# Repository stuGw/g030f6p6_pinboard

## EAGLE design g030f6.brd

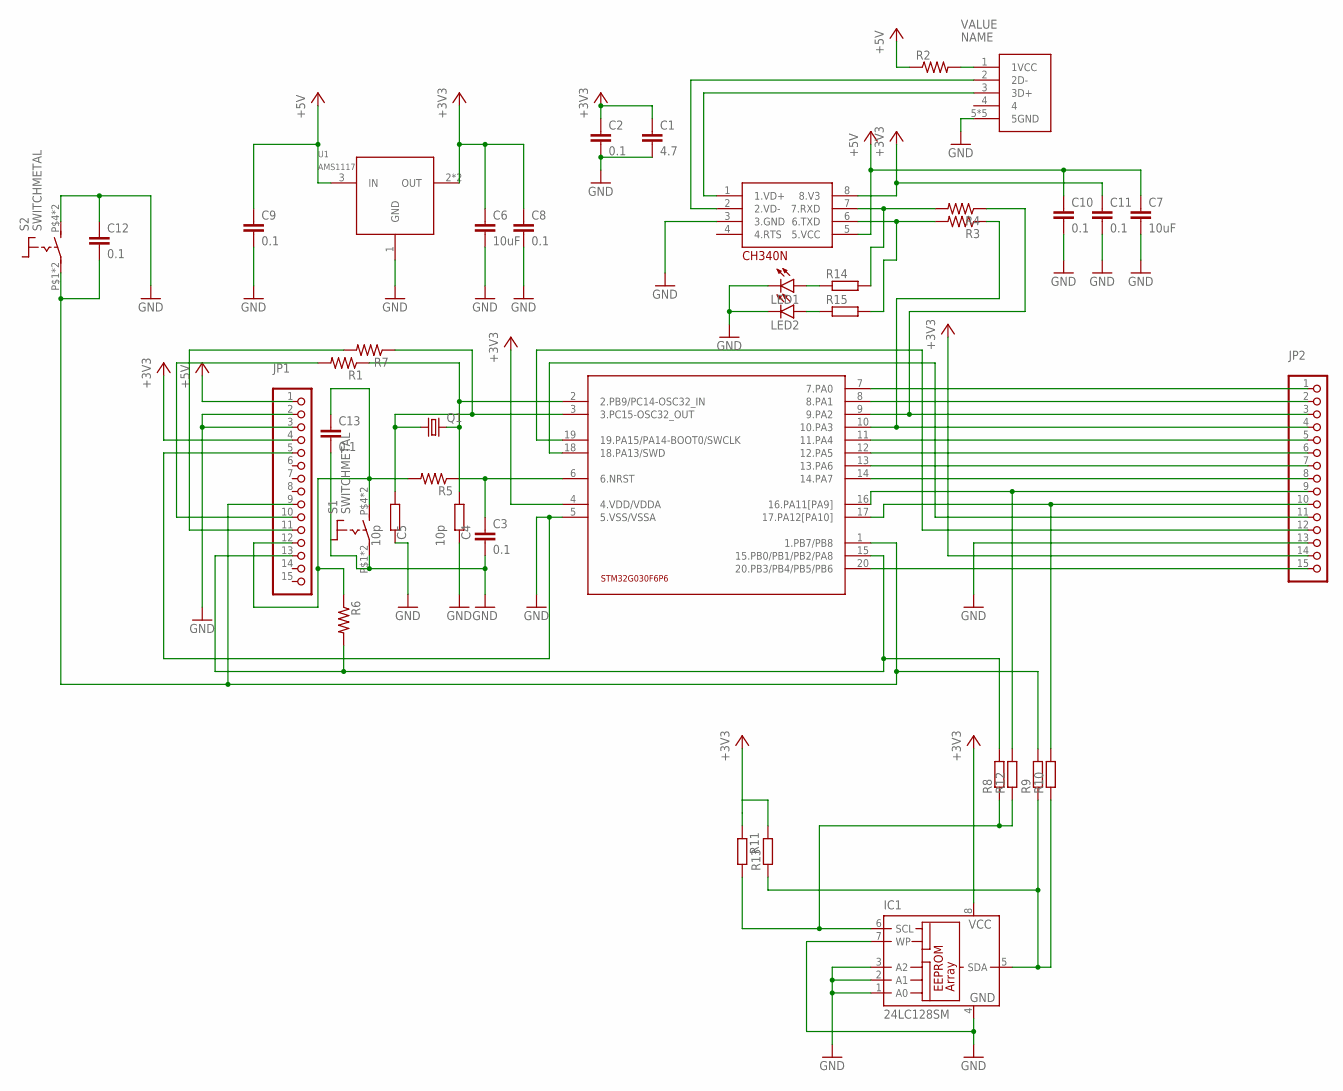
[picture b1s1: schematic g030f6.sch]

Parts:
C1: 4.7; C0805
C2, C3, C8, C9, C10, C11, C12, C13: 0.1; C0402
C4, C5: 10p; R0402
C6, C7: 10uF; C0805
CONN1: MICROUSB; MICROUSB5
IC1: 24LC128SM; SO-08M
JP1, JP2: PINHD-1X15; 1X15
LED1, LED2: LEDSML0603; SML0603
Q1: CRYSTALTC26V; TC26V
R1, R3, R4, R5, R6, R7: R-US_R0402; R0402
R2: R-US_R2010; R2010
R8, R9, R10, R11, R12, R13: R-EU_R0603; R0603
R14, R15: R-EU_R0402; R0402
S1, S2: SWITCHMETAL; SWMET
U1: AMS1117; SOT223
U$1: STM32GO3OF6P6; TSSOP20
U$3: CH340N; SO-8

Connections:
+3V3: C1.1, C2.1, C6.1, C8.1, C11.1, IC1.8 (VCC), JP1.4, JP2.14, R11.1, R13.2, U1.2 (OUT), U1.4 (OUT), U$1.4 (4.VDD/VDDA), U$3.8 (8.V3)
+5V: C7.1, C9.1, C10.1, JP1.1, R2.1, U1.3 (IN), U$3.5 (5.VCC)
GND: C1.2, C2.2, C3.2, C4.2, C5.2, C6.2, C7.2, C8.2, C9.2, C10.2, C11.2, C12.1, C13.2, CONN1.5 (5GND), CONN1.P$1 (5GND), CONN1.P$2 (5GND), CONN1.P$6 (5GND), CONN1.P$7 (5GND), IC1.1 (A0), IC1.2 (A1), IC1.3 (A2), IC1.4 (GND), IC1.7 (WP), JP1.2, JP1.3, JP1.5, JP2.13, LED1.C, LED2.C, S1.P$1, S1.P$1@1, S2.P$4 (S), S2.P$4@1 (S), U1.1 (GND), U$1.5 (5.VSS/VSSA), U$3.3 (3.GND)
unnamed: C4.1, Q1.2, R1.1, U$1.2 (2.PB9/PC14-OSC32_IN)
unnamed: C5.1, Q1.1, R7.1, U$1.3 (3.PC15-OSC32_OUT)
unnamed: JP1.13, R6.2, R8.2, U$1.15 (15.PB0/PB1/PB2/PA8)
unnamed: C13.1, JP1.12, R5.2, R6.1, S1.P$4 (S), S1.P$4@1 (S)
unnamed: JP2.11, U$1.18 (18.PA13/SWD)
unnamed: JP2.12, U$1.19 (19.PA15/PA14-BOOT0/SWCLK)
unnamed: C3.1, R5.1, U$1.6 (6.NRST)
unnamed: IC1.6 (SCL), R8.1, R11.2, R12.1
unnamed: JP2.4, R3.1, U$1.10 (10.PA3)
unnamed: JP2.3, R4.1, U$1.9 (9.PA2)
unnamed: LED1.A, R14.1
unnamed: LED2.A, R15.1
unnamed: JP2.5, U$1.11 (11.PA4)
unnamed: JP2.6, U$1.12 (12.PA5)
unnamed: JP2.7, U$1.13 (13.PA6)
unnamed: JP2.8, U$1.14 (14.PA7)
unnamed: JP2.9, R12.2, U$1.16 (16.PA11[PA9])
unnamed: JP2.10, R10.2, U$1.17 (17.PA12[PA10])
unnamed: CONN1.1 (1VCC), R2.2
unnamed: JP1.11, R7.2
unnamed: JP2.15, U$1.20 (20.PB3/PB4/PB5/PB6)
unnamed: CONN1.2 (2D-), U$3.2 (2.VD-)
unnamed: CONN1.3 (3D+), U$3.1 (1.VD+)
unnamed: JP2.1, U$1.7 (7.PA0)
unnamed: R3.2, R15.2, U$3.6 (6.TXD)
unnamed: R4.2, R14.2, U$3.7 (7.RXD)
unnamed: JP2.2, U$1.8 (8.PA1)
unnamed: JP1.10, R1.2
unnamed: C12.2, JP1.9, R9.2, S2.P$1, S2.P$1@1, U$1.1 (1.PB7/PB8)
unnamed: IC1.5 (SDA), R9.1, R10.1, R13.1

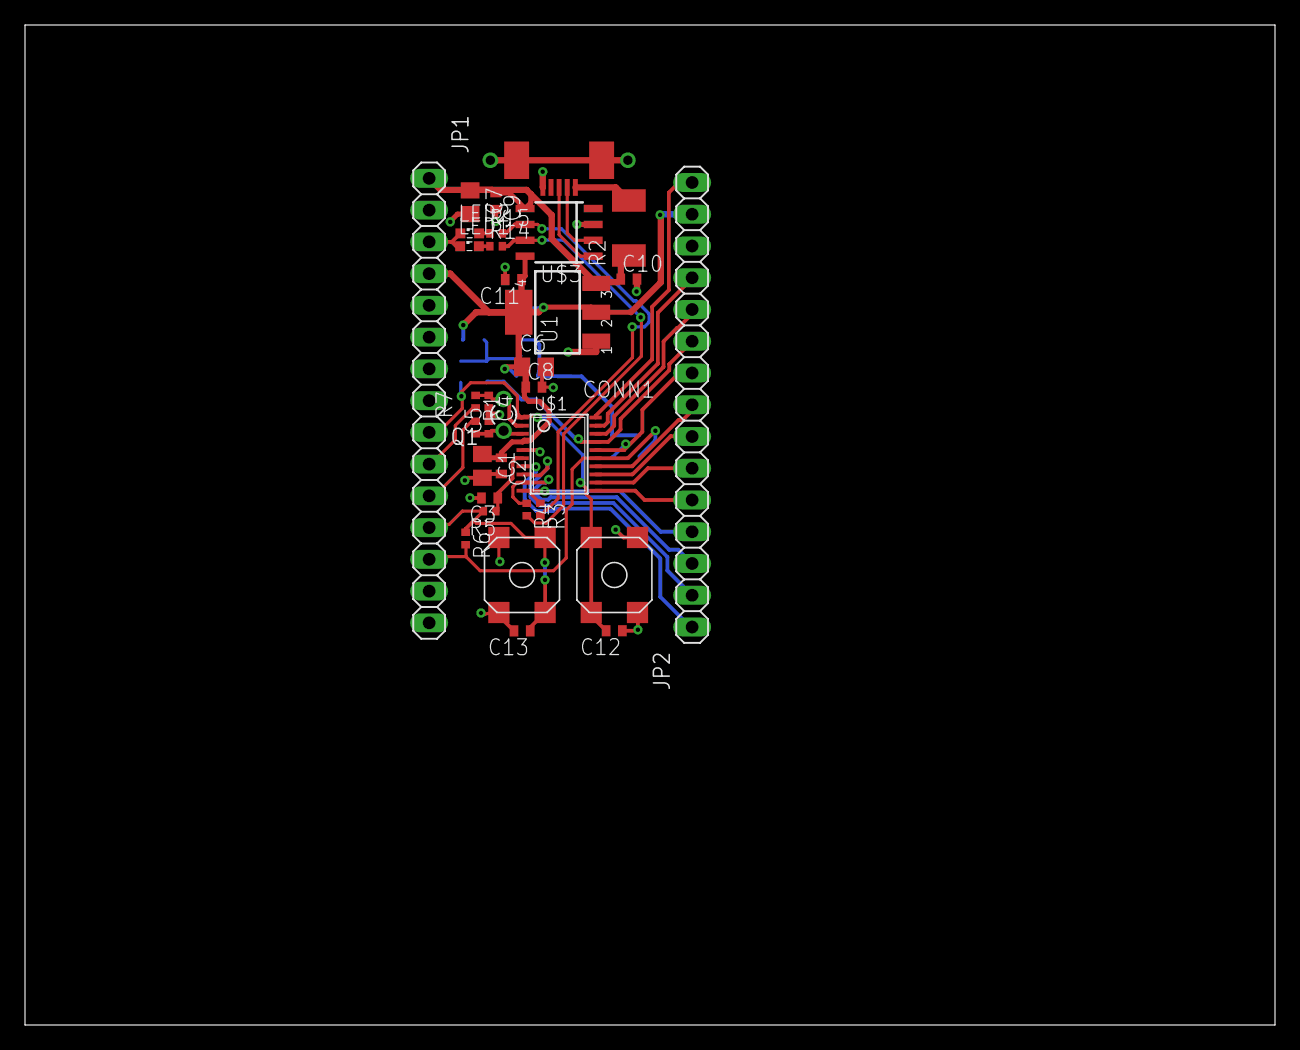
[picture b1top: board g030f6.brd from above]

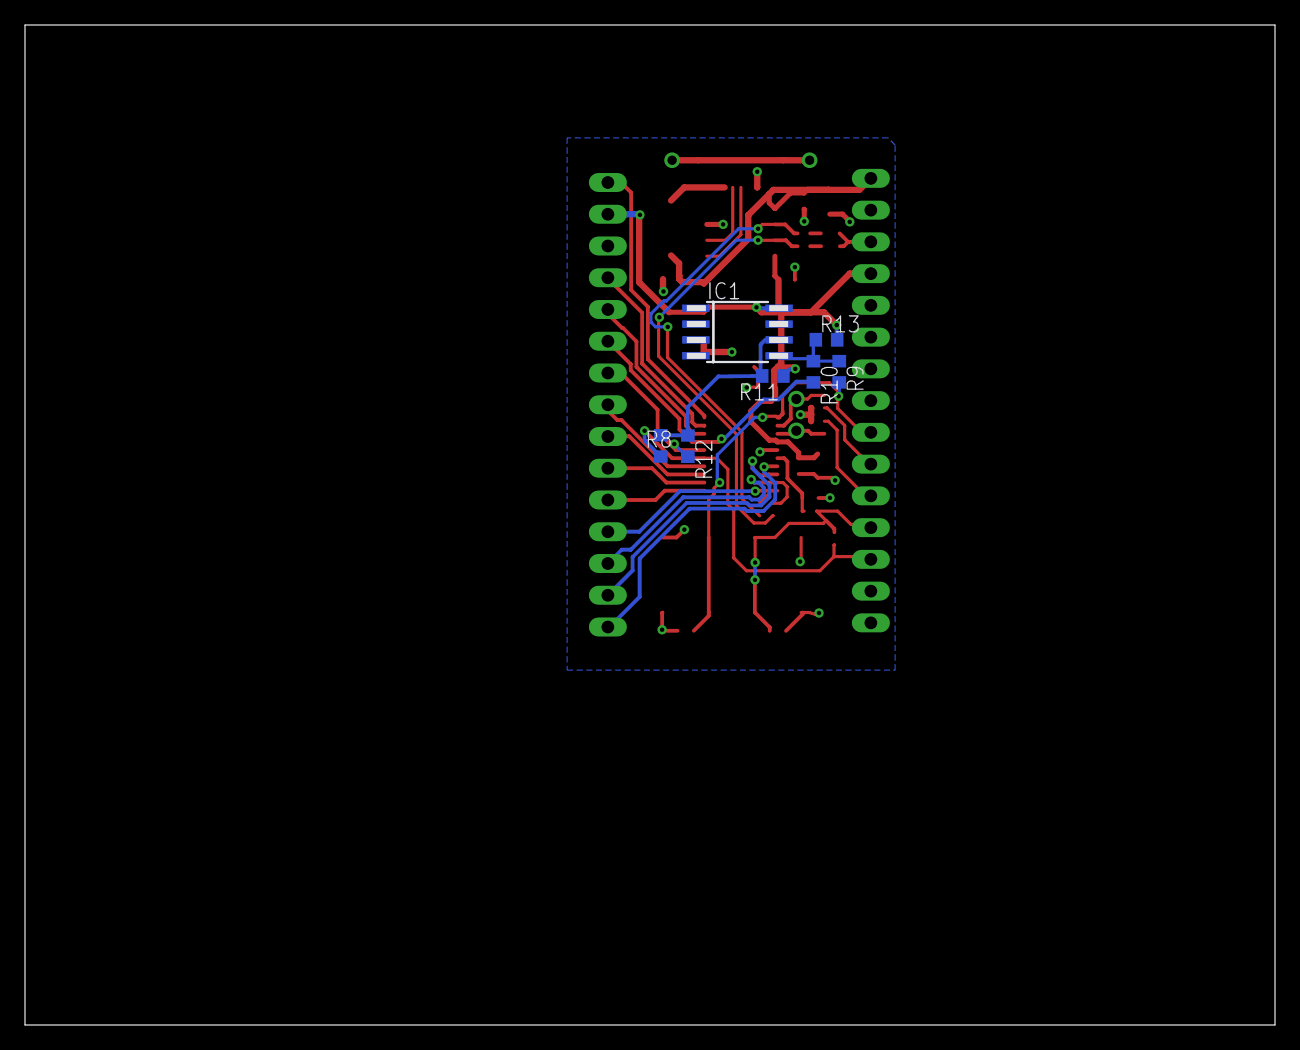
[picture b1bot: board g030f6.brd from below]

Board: 2 copper layers, 100.0 x 80.0 mm, 40 parts (7 on the bottom side), 33 nets.

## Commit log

2022-05-20 first
2022-05-21 checked, TODO minimize size
